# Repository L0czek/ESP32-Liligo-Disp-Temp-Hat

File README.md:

# ESP32 LilyGO Display + Temperature Hat

A KiCad 10 hat for the **LilyGO T-Relay-8** (ESP32, 8 relays). It adds 8 thermocouple
inputs, heater current measurement, a 1-Wire port and a connector for a front panel
(1.3" SH1106 OLED with rotary encoder and buttons).

- Base board: [LilyGO T-Relay-8](https://www.amazon.pl/dp/B0B6TY79WN) —
  [vendor repo](https://github.com/Xinyuan-LilyGO/LilyGo-T-Relay) (schematic, DXF outline, pinmap)
- Front panel: [1.3" SH1106 OLED with encoder and buttons](https://allegro.pl/oferta/wyswietlacz-oled-1-3-sh1106-bialy-z-enkoderem-przyciskami-panel-sterowania-18116662587)
- Load: 24 V heaters switched by the T-Relay relays, about 18.75 A in total: several heaters, each under 10 A, one per relay

> **Branches.** `master` is the current board: routed, 0 unconnected, no DRC errors on copper.
> `hand-routed` is the first hand routing exactly as drawn. `scripted-routing` is an earlier,
> fully scripted board with a different layout. Both are kept for reference only.

## Blocks

| Block | Parts | Notes |
|---|---|---|
| Thermocouple front end | J2–J9, D1–D4, R14–R29, U1, U3 (TMUX1108), U2 (MAX31856) | Each terminal has an ESD clamp and 100 Ω in series (see "Thermocouple input protection"). U1 muxes the `+` legs, U3 the `−` legs, into one MAX31856 over SPI. Input filter: R1 100 Ω, R2 300 Ω, C1 100 nF differential, C2/C3 10 nF to GND. |
| I/O expander | U4 (PCF8574A), U5 (74LVC1G04), JP1–JP3 | Mux address and enable, MAX31856 status, two panel buttons. |
| Front panel | J10 (1x9 socket) | I²C display, encoder, buttons. The panel plugs in on a right-angle header and lies flat past the hat's lower edge. |
| Heater current | J11, R6 (shunt), U6 (INA226) | High-side shunt in the +24 V feed, read over I²C. See "Heater current sensing". |
| 1-Wire | J12 (JST PH 3-pin), R12, U7, U8 | External DS18B20 probes on J12, plus two on-board DS18B20Z (U7, U8) for cold-junction sensing. Recommended; the board works without them, less accurately. |
| Supply | L1, C10–C14 | `VCC` = 3V3 from the T-Relay; `VAA` = analog rail for U2, filtered by ferrite bead L1. |

## J1: connection to the T-Relay-8

J1 is a 2x11 socket soldered on the **bottom** of the hat, facing down onto the T-Relay's pin
header P5. Its footprint is on the back side of the board, so the board file shows what is
really built: pads, silkscreen, courtyard and 3D model are all on the bottom.

**J1's pin numbers are the same as LilyGO's P5 pin numbers.** J1 pin n mates with P5 pin n.
Checked against the official T-Relay-8 schematic (`Schematic/T_Relay8_ESP32.pdf`, header P5),
the vendor pinmap image and the silkscreen labels in the vendor DXF; all three agree. The
schematic and the pinmap were downloaded and compared again on 2026-11-12. This is a check
against documents only: no real T-Relay was at hand to put a meter on. On the
board, pad 2 (3V3) is at (121.54, 95.89) and pad 1 (GND) at (121.54, 93.35), which is the
right-hand end of the header seen from above with the relays on the left.

(Before 2026-11-12 the footprint sat on the front layer with the two rows numbered the other
way round, pin 1 = 3V3. That was electrically the same but drew the socket on the wrong side.)

### How the hat sits on the T-Relay-8

From the vendor DXF and STEP model (T-Relay board is 85 × 170 mm). With J1 mated, a point on
the hat at (x, y) is above the T-Relay point (x − 41.54, y − 19.99) mm, measured from the
T-Relay's top-left corner with the relays on the left.

- **The hat's top and right edges are flush with the T-Relay's.** The outline is 46.0 × 99.7 mm
  (it was 48.3 mm wide; 2.3 mm were cut off on the right). It covers the T-Relay from
  x = 39.0 mm to the right edge and from the top edge down to y = 99.7 mm.
  - Relative to the original design, everything except J1 sits 3.3 mm further left and
    3.5 mm further down on the sheet; J1 and `REF1` did not move.
  - The T-Relay's top edge is at hat y = 19.99 and its right edge at hat x = 126.54.
- **Relays** are 15.7 mm tall and end at x = 37.7 mm, 1.3 mm from the hat's left edge.
- **The ESP32 antenna is not under the hat.** The module sits at T-Relay x = 59–77.5 mm,
  y = −6.4 to 25.6 mm; its antenna end sticks out past the T-Relay's top edge, where the hat
  stops.
- **Mounting holes** are M3 with a 6.4 mm pad, as in the original. H1 is at (122.7, 23.8) and
  H3 at (122.9, 104.1): both had to move in from the cut edge, and H3 also up, because the
  corner beside J10 is too narrow for it. H2 and H4 are at their original places.
  - H2 is above the T-Relay's reset button (S1), so it cannot take a resting spacer. Known
    and accepted: H2 stays where it is, without a spacer. The button is covered by the hat;
    the T-U2T programmer resets the ESP32 through the USB-C connector instead.
  - The other three, the terminal pins, the J11 pins and the parts on the back were checked
    on 2026-11-12 against the vendor STEP model, DXF and top-view photo
    (`image/T-Relay8.jpg`): all clear at an 11 mm gap, and down to about 6 mm. Under H3, H4,
    the J11 pins and the J10 pins the photo shows bare board. No real board was at hand.
  - **H1 is tight:** its pad edge is 0.4 mm from the ESP32 module in the model, and in the
    photo the spacer reaches the module's edge pads to within the 1 mm accuracy of the
    overlay. A nylon spacer there is harmless; a metal one is not.
  - Two of the T-Relay's own 4 mm mounting holes are under the hat, at (91.57, 37.57) and
    (89.64, 93.44): screw the T-Relay down before plugging the hat on.
  - Plain 4 mm holes (the T-Relay's size) were tried and do not help: the stock footprint's
    keep-out is 8.5 mm across, more than the M3 pad, and H4 would not fit between J9 and J10.
  - **Use nylon spacers.** The spacers only rest on the T-Relay's surface and the hole pads
    are GND, so a metal spacer could wear through the solder mask onto a track.
- **J12 sits above the ESP32 module's top end**, so the 1-Wire cable leaves across the antenna.
  This was looked at and accepted; moving J12 to the top-left corner was tried and rejected.

| J1 = P5 pin | ESP32 | Signal | Notes |
|---|---|---|---|
| 1, 3 | GND | GND | |
| 2, 4 | 3V3 | VCC | |
| 5 | IO14 | TC_SCK | LilyGO names this net `GPIO14/CLK` |
| 6 | IO2 | TC_MISO | Boot strap. LilyGO: `GPIO2/MISO` |
| 7 | IO15 | TC_MOSI | Boot strap. LilyGO: `GPIO15/MOSI` |
| 8 | IO4 | TC_CS | Pulled up by R13 (4.7 kΩ) so the MAX31856 stays deselected, and off IO2, during boot |
| 9 | IO35 | ENCODER_B | Input-only |
| 10–14 | NC | — | Not connected on the T-Relay |
| 15 | IO39 | JOYSTICK_PUSH | Input-only. See note below. |
| 16 | IO36 | free | Input-only, ADC1. See note below. |
| 17 | IO34 | ENCODER_A | Input-only |
| 18 | GND | GND | |
| 19 | IO26 | EXPANDER_INT | Pulled up by R3 |
| 20 | IO27 | I2C_SDA | |
| 21 | IO22 | ONEWIRE | The only free bidirectional pin; 1-Wire needs one |
| 22 | IO23 | I2C_SCL | |

- IO34, IO35, IO36 and IO39 are input-only and have no internal pull-ups or pull-downs.
  The front panel provides 10 kΩ pull-ups for the encoder and push button.
- IO36 and IO39 can see very short spurious low pulses when the ESP32's ADC is used or Wi-Fi
  runs with modem sleep (documented by Espressif). Do not use an edge interrupt on
  JOYSTICK_PUSH without debouncing; polling or a debounce of a millisecond or more is enough.
  This is why the push button, not an encoder phase or the expander interrupt, sits on IO39.
- On the T-Relay-8 none of the header GPIOs connect to anything else on the board.
  Relays use IO21, IO19, IO18, IO5, IO12, IO13, IO32, IO33; IO25 is the red LED.

## Heater current sensing

```
PSU+ → J11.1 (24V_IN) → R6 → J11.2 (24V_OUT) → relay COMs → heater → PSU−
```

- The hat sits in the positive feed. No heater current flows in the hat's GND.
- **PSU− must be connected to the T-Relay's GND.** The hat has no terminal for PSU−, so the
  INA226 measures the 24 V rail against the T-Relay's ground. Powering the T-Relay from the
  same 24 V supply does this automatically. With the T-Relay on USB or on a separate isolated
  supply while the heater supply is live, the INA226 inputs float outside their −0.3 to 36 V
  range: readings are meaningless and the chip can be damaged. The T-Relay accepts 12–24 V DC,
  and the plan is to run it from the heater supply, but that is not confirmed: treat this
  as an installation rule.
- J11 is a Phoenix MKDS5/2-6.35 screw terminal block (fixed, not pluggable).
- R6 is a 1 mΩ 4-terminal (Kelvin) shunt, Vishay WSK2512 footprint. Pads 1/4 carry the current,
  pads 2/3 go only to the INA226 inputs. At 18.75 A: 18.75 mV, 0.35 W.
- U6 is an INA226AIDGS at I²C address `0x40` (A0 = A1 = GND), powered from `VCC`, decoupled by C14.
  `Vbus` is on `24V_OUT`, so firmware can also read the supply voltage after the shunt.
  The `Alert` pin is not connected: firmware polls over I²C, and the relays are driven by the
  ESP32 anyway, so a hardware alert would not switch anything off faster.
- R7/R8 (10 Ω) and C15 (100 nF) filter the sense inputs (TI's recommended input filter, corner
  about 80 kHz). They keep relay switching spikes and RF out of the converter and limit current
  into the inputs during transients. 10 Ω is TI's upper limit; the gain error it adds is negligible.
- The review asked for 2 mΩ / 3 W. 1 mΩ was chosen to keep the dissipation low (0.35 W);
  resolution is still about 2.5 mA per LSB.
- Two parts fit (see "BOM"): the true four-terminal Vishay WSK2512 from Mouser, which the
  footprint was drawn for, or an ordinary two-terminal 1 mΩ strip resistor from TME, which
  works on the same pads with a gain error of a few percent.

The board controls several heaters independently, one per relay, each under 10 A; 18.75 A
(450 W at 24 V) is their **sum** (confirmed by the user, 2026-11-12). `24V_OUT` feeds the COM
terminals of all heater relays, and J11 and R6 carry the total.

- The relays are HRS4H-S-DC5V, rated 10 A at 24 V DC per contact (vendor datasheet
  `docs/HRS4-DC5V.pdf`). A single 18.75 A heater on one relay would not be acceptable.
- The INA226 measures the total only. Firmware can get a single heater's current from the
  step in the reading when that relay switches.

## Thermocouple input protection

**Use insulated (ungrounded-junction) thermocouple probes only.** The protection below covers
static discharge and switching spikes. It does not cover a thermocouple line held on 24 V:
that would destroy the clamp and probably the multiplexer.

```
terminal J2–J9 ──────┬── 100 Ω ── TCn± ── TMUX1108 ── ... ── MAX31856
                     │
              ESD clamp to GND
```

- The MAX31856 inputs withstand ±45 V, but the TMUX1108 in front of it only allows −0.5 V to
  VDD + 0.5 V on its signal pins and is rated for 2 kV ESD, so the multiplexers are the weak point.
- D1–D4: Nexperia PESD5V0L4UG, four clamps per package, one package per pair of terminals
  (D1: J2/J3, D2: J4/J5, D3: J6/J7, D4: J8/J9). Place each one right at its terminals.
  The schematic symbol is KiCad's generic 4-diode array (`SP0504BAJT`: same pinout, same
  SOT-353 footprint) with the value set to PESD5V0L4UG, because the library's own PESD symbol
  is split into four separate diode units and reads badly.
- R14–R29: 100 Ω in each line, between the clamp and the multiplexer.
- R2 is 300 Ω, not 100 Ω. The bias point is at the multiplexer output, so both added 100 Ω
  resistors of a channel end up in the T+ path (R1 + 2 × 100 Ω). The MAX31856 datasheet
  ("Effect of Series Resistance") says to match the two paths: offset = I_B × ΔR_S + ΔI_B × R_S,
  with I_B up to 65 nA. Unmatched, 200 Ω would add up to 13 µV; matched, about 2 µV (0.05 °C, type K).
- Series resistance per input stays far below 5 kΩ, so the fast open-circuit detection mode
  (`OCFAULT = 01`) still applies.
- Clamp leakage (25 nA per TME's listing, at 5 V; lower at the 0.7 V the lines sit at) flows
  through 100 Ω at most: under 3 µV.

Considered and not used: 2.2 kΩ + BAV199 rail clamps + 100 Ω per line, which would survive a
continuous 24 V on any line. It needs 48 parts, R2 of about 4.75 kΩ, the slower open-circuit
mode, and costs up to about 20 µV (0.5 °C) worst case.

## Cold-junction sensing

A thermocouple reading is the tip temperature minus the temperature of the terminals J2–J9,
so an error in the terminal temperature goes into every reading one for one. The MAX31856
uses its own internal sensor for this, which measures the chip, not the terminals.

U7 and U8 are two DS18B20Z on the `ONEWIRE` bus (shared with J12, pulled up by R12). Firmware
can read them, interpolate along the terminal row and write the result into the MAX31856's
cold-junction register in place of the internal sensor.

- **Fit them (recommended).** U2 is about 28 mm from the terminals, and the terminals sit
  1.3 mm from the relays, which warm up when energised. U2's internal sensor does not see
  that.
- **The board still works without them.** Leave U7, U8, C16 and C17 unfitted and let the
  MAX31856 use its internal sensor; nothing else changes, and 1-Wire on J12 is unaffected.
  They are not flagged DNP in the schematic. What it costs:
  - Every channel reads wrong by the temperature difference between U2 and its terminal,
    one for one. Expect a few °C; this has not been measured.
  - The error is not a fixed offset. It depends on which relays are on and for how long,
    and it differs along the row, so it cannot be calibrated out.
  - Fine for coarse control or for watching trends; not for readings that have to be
    right to a degree.
- **Moving U2 closer was looked at and rejected** (2026-11-12). The only free spot is
  mid-row beside U3, about 12 mm from the terminal pins. It means moving eight parts and
  rerouting about 16 nets, and one sensor still cannot see the gradient along a 94 mm row.
  With U7/U8 fitted, U2's position does not matter.
- Known limit: R6 and J11 dissipate about 0.5 W level with J6/J7, mid-row, where the two
  end sensors cannot see it. Worth one measurement at full heater current on the built board.
- Layout: one sensor at each end of the J2–J9 row, close to the terminals, each with its
  capacitor (C16, C17) next to it. Keep the shunt, J11, L1 and the 24 V copper away from the
  terminals and from U2, and group the terminals close to U2 if possible.

## U4 (PCF8574A) port map

Address `0x38` with JP1–JP3 in their default position (A0–A2 to GND).

| Port | Signal | Direction |
|---|---|---|
| P0–P2 | TC_A0–TC_A2 (mux channel n = `TCn` = terminal J(n+2): J2 is channel 0, J9 is channel 7) | out |
| P3 | mux enable, inverted by U5: P3 low = muxes on. High at power-up, so muxes start disabled. | out |
| P4 | JOYSTICK_CONFIRM | in |
| P5 | JOYSTICK_BACK | in |
| P6 | TC_DRDY | in |
| P7 | TC_FAULT | in |

## Firmware notes

- **After switching the thermocouple channel, wait 1–2 ms before starting a conversion.**
  The original review said about 100 µs. Since then each line got 100 Ω and R2 became 300 Ω,
  so C1 (100 nF) now charges through about 610 Ω plus the probe's own resistance: a time
  constant of about 65 µs. Settling a 20 mV step between two channels to 1 µV takes about
  ten time constants, 0.7 ms.

## J10: front panel

| Pin | Signal | Pin | Signal |
|---|---|---|---|
| 1 | JOYSTICK_CONFIRM | 6 | ENCODER_B |
| 2 | I2C_SDA | 7 | JOYSTICK_BACK |
| 3 | I2C_SCL | 8 | GND |
| 4 | JOYSTICK_PUSH | 9 | VCC |
| 5 | ENCODER_A | | |

### Panel module

Generic "1.3 inch OLED + EC11 encoder" module, 9-pin header, about 65 × 35 mm, four M3 holes.
Details below are read from the seller manual's schematic (a low-resolution image of the
generic module, not measured on our unit):

- Display: SH1106, I²C address 0x3C, 3.3 V supply only (no regulator shown).
- I²C: 10 kΩ pull-ups to 3V3 on SDA and SCL on the module.
- Encoder A/B (TRA/TRB) and push (PSH): each has a 10 kΩ pull-up to 3V3, 100 nF to GND
  and a 100 Ω series resistor. Switches close to GND (active-low).
- CON (KEY1) and BAK (KEY0) buttons: 10 kΩ pull-up, 100 nF to GND, switch to GND.
- Header order is CON, SDA, SCL, PSH, TRA, TRB, BAK, GND, VCC, which matches J10 pin 1–9.
  The module's own schematic numbers the header the other way round (pin 1 = 3V3).

**Pin order checked against the module's silkscreen** in the seller's photos (2026-11-12),
both sides:

- Front, left to right with the header along the top edge: `CON SDA SCL PSH TRA TRB BAK GND
  VCC`. The square pad is the VCC end.
- Back, same pads: `CONFIRM OLED_SDA OLED_SCL ENCODER_PUSH ENCODER_A ENCODER_B BACK GND 3V3`.
- J10 pins 1–9 carry exactly these signals in this order.
- A straight header comes loose with the module. It is not used: see below.

Consequences: the hat's pull-ups for the encoder and push button (R9–R11, 10 kΩ) are
back-ups, marked do-not-populate. Fit them only if a panel without pull-ups is used. With the panel connected, the I²C bus already has the
panel's 10 kΩ in parallel with R4/R5.

### How the panel connects

**The panel gets a right-angle 1 × 9 pin header and plugs straight into J10. It lies flat,
as an extension of the hat past its lower edge, screen up.** Nothing changes on the hat.

- **Pin order is right.** Seen from above, the panel lies the same way round as in a front
  photo (header along the top edge, CON on the left), and J10 has pin 1 on the left: CON
  lands on pin 1, VCC on pin 9. This matches the `CON` and `VCC` labels on the hat.
- **Solder the header on the panel's back**, pins pointing out past the header edge. The
  panel then sits about 3 mm above the hat's surface, about 15 mm above the T-Relay.
- **Position** (sheet coordinates): about x = 87.6–154.1, y = 121.4–156.8.
  - 8 mm clear of the relays on the left.
  - Only low parts of the T-Relay are under it (the tallest are 3.8 mm).
  - It ends before the T-Relay's USB-C connector and power terminal.
  - **It sticks out about 28 mm past the right edge of both boards**, because the panel is
    66 mm wide and its header is near its left end.
- **It needs support.** On its own it hangs on the nine pins, and pressing the encoder or
  the buttons levers on them from up to about 45 mm away. The panel's two left mounting
  holes are above the T-Relay and can take spacers of about 15 mm; the two right ones are
  beyond the boards' edge.
- The display reads the right way up for someone standing at the T-Relay's power-input end.
- It covers the lower part of the T-Relay (optocouplers, relay indicator LEDs).

The heights and the stand-off from the hat's edge assume a typical 2.54 mm right-angle
header and were not measured; the mounting-hole positions were read off the photo.

Other ways of connecting it, and why not:

- **A straight header, panel standing up at the hat's edge and facing outwards:** pin order
  reversed, VCC on J10 pin 1, and the panel's corner hits a relay. This is the trap: it is
  what a straight header naturally gives.
- **A straight header, panel hanging down and facing outwards:** right pin order, but it
  needs about 32 mm below J10 and the T-Relay is 12.6 mm below.
- **A 1:1 cable:** also correct electrically (J10 pin 1 to CON … pin 9 to VCC), if the
  panel should go somewhere else, for example on an enclosure's front. A plain pin strip
  is not keyed, so watch which end is pin 1.

## BOM

TME prices are gross PLN at the quantity needed, checked 2026-11-12. Rules used: common
resistor and capacitor values and plain pin headers/sockets are assumed to be on hand and
are only listed, not priced; everything else is the cheapest part that is in stock and sold
in prototype quantities.

The parts are split over two orders, TME and Mouser, because the MAX31856 is only at Mouser.

- TME prices are live from TME's API, gross.
- Mouser prices and stock were read from mouser.pl on 2026-11-12, as displayed there. The
  pages did not say whether VAT is included; Mouser normally shows net prices.
- **→ M** in the TME table marks a part that TME has but that is better bought from Mouser,
  since a Mouser order is needed anyway. The reason is in the notes.

### Order 1: TME

| Ref | Qty | Part | TME | Price | → M | Notes |
|---|---|---|---|---|---|---|
| U1, U3 | 2 | TI TMUX1108PWR, TSSOP-16 | [`TMUX1108PWR`](https://www.tme.eu/pl/details/TMUX1108PWR/) | 2 × 28.29 | **→ M** | TME has only 12 left. Mouser has 5,948 at 19.36 zł. |
| U4 | 1 | TI PCF8574APWR, TSSOP-20 | [`PCF8574APWR`](https://www.tme.eu/pl/details/PCF8574APWR/) | 9.40 | **→ M** | 6.03 zł at Mouser. Stands in for the NXP PCF8574ATS in the schematic, which TME does not list. Pinout checked against TI's datasheet (DGV/PW package, figure 4-3): all 20 pins match the schematic, and the footprint is the same 4.4 mm, 0.65 mm pitch package. |
| U5 | 1 | TI SN74LVC1G04DBVR, SOT-23-5 | [`SN74LVC1G04DBVR`](https://www.tme.eu/pl/details/SN74LVC1G04DBVR/) | 0.64 | | |
| U6 | 1 | TI INA226AIDGSR, VSSOP-10 | [`INA226AIDGSR`](https://www.tme.eu/pl/details/INA226AIDGSR/) | 11.06 | | |
| U7, U8 | 2 | DS18B20Z+, SO-8 | [`DS18B20Z+`](https://www.tme.eu/pl/details/DS18B20Z%2B/) | 2 × 32.94 | | Recommended, not required: see "Cold-junction sensing". C16/C17 go with them. |
| D1–D4 | 4 | Nexperia PESD5V0L4UG, SOT-353 | [`PESD5V0L4UG.115`](https://www.tme.eu/pl/details/PESD5V0L4UG.115/) | 4 × 1.23 | | |
| R6 | 1 | Eaton MSMA2512R0010FEN, 1 mΩ 1 % 2 W metal strip, 2512 | [`MSMA2512R0010FEN`](https://www.tme.eu/pl/details/MSMA2512R0010FEN/) | 2.46 | **→ M** | Works (see "R6 on the four-terminal footprint"), but it is a two-terminal part. Mouser has the part the footprint was drawn for: Vishay WSK25121L000FEA, in the Mouser table. Buy one or the other. |
| L1 | 1 | TDK MPZ2012S601ATD25, 600 Ω at 100 MHz, 2 A, 0805 | [`MPZ2012S601ATD25`](https://www.tme.eu/pl/details/MPZ2012S601ATD25/) | 0.38 | | |
| R2 | 1 | Yageo RC0805FR-07300RL, 300 Ω 1 %, 0805 | [`RC0805FR-07300RL`](https://www.tme.eu/pl/details/RC0805FR-07300RL/) | 0.20 | | Listed because 300 Ω is not an E12 value. |
| J11 | 1 | Phoenix MKDS5/2-6.35, 32 A | [`MKDS5/2-6.35`](https://www.tme.eu/pl/details/MKDS5_2-6.35/) | 8.04 | | Exact fit on the stock `TerminalBlock_MetzConnect_Type701_RT11L02HGLU` footprint (hole size confirmed on the Phoenix drawing by the user). |
| J12 | 1 | JST S3B-PH-SM4-TB | [`S3B-PH-SM4-TB`](https://www.tme.eu/pl/details/S3B-PH-SM4-TB/) | 2.29 | | |
| J12 cable end | 1 + 3 | JST PHR-3 housing and SPH-002T-P0.5L/C crimp contacts | [`PHR-3`](https://www.tme.eu/pl/details/PHR-3/), [`SPH-002T-P0.5L/C`](https://www.tme.eu/pl/details/SPH-002T-P0.5L_C/) | 0.29 + 3 × 0.44 | | Only if the 1-Wire cable is made up by hand. |

Everything in this table: about 163 zł. With the three **→ M** lines moved to Mouser: about 95 zł.

### Order 2: Mouser

| Ref | Qty | Part | Mouser no. | Price | Stock | Notes |
|---|---|---|---|---|---|---|
| U2 | 1 | Analog Devices MAX31856MUD+, TSSOP-14 | `700-MAX31856MUD+` | 53.94 | 4,846 | The reason for this order: TME lists only the MAX31855/MAX31850. |
| J2–J9 | 8 | Phoenix MCV 1,5/2-G-5,08 header (Phoenix no. 1836299) | `651-1836299` | 8 × 3.22 | 1,038 | TME: stock 0. |
| J2–J9 plugs | 8 | Phoenix MC 1,5/2-ST-5,08 BK screw plug, black (Phoenix no. 1981238) | `651-1981238` | 8 × 8.80 | 41 | The usual green one (1836079, `651-1836079`, 9.11) has stock 0 at both TME and Mouser; Mouser expects it on 2026-12-11. The black one is the same plug. |
| R6 | 1 | Vishay WSK25121L000FEA, 1 mΩ 1 % 1 W, four-terminal 2512 | `71-WSK25121L000FEA` | 9.33 | 4,273 | Instead of the TME part: the exact part for the footprint, a true four-terminal shunt. |
| U1, U3 | 2 | TI TMUX1108PWR | `595-TMUX1108PWR` | 2 × 19.36 | 5,948 | Instead of TME, see above. |
| U4 | 1 | TI PCF8574APWR | `595-PCF8574APWR` | 6.03 | 183 | Instead of TME, see above. |

The three lines only Mouser can supply (U2, headers, plugs): about 150 zł. With the three
**→ M** lines as well: about 204 zł.

Every part on the board has a source.

### R6 on the four-terminal footprint

TME sells four-terminal 2512 shunts (Bourns CSS2H/CSI2H-2512K, Vishay WSK2512) only in
reels or lots of 173 and more, so the pick is an ordinary two-terminal strip resistor.

- **It fits and connects correctly.** On the WSK2512 footprint each end has a current pad
  (3.3 × 2.03 mm) and a sense pad (1.4 × 0.76 mm) side by side across the part's width, both
  reaching past the part's end. A 2512 end termination is as wide as the part, so it lands
  on both. The two pads of one end are then joined by the termination itself, which is the
  intended connection.
- **The measurement is still close to four-wire.** The sense track leaves from its own pad
  under the termination, so it does not share the solder joint or the copper that carries
  the 19 A.
- **What is lost:** the sense point is on the termination instead of at the resistive
  element, so the reading includes a little termination resistance. Expect a fixed gain
  error of a few percent and somewhat more drift with temperature than a true
  four-terminal part. Calibrate the gain once in firmware. For monitoring heater current
  this is not a problem.

### Assumed on hand

| Ref | Qty | Value | Footprint |
|---|---|---|---|
| R1, R14–R29 | 17 | 100 Ω | 0805 |
| R3 | 1 | 10 kΩ | 0805 |
| R4, R5, R12, R13 | 4 | 4.7 kΩ | 0805 |
| R7, R8 | 2 | 10 Ω | 0805 |
| C1, C4–C9, C14–C17 | 11 | 100 nF | 0805 |
| C2, C3 | 2 | 10 nF | 0805 |
| C10–C13 | 4 | 22 µF, 10 V or more, X5R/X7R | 1206. If not on hand: [`GRM31CR61E226KE15L`](https://www.tme.eu/pl/details/GRM31CR61E226KE15L/), 25 V X5R, 1.67 at 10 pieces. |
| J1 | 1 | 2 × 11 socket, 2.54 mm, 8.5 mm high, soldered on the **bottom** | |
| P5 on the T-Relay | 1 | 2 × 11 pin header, 2.54 mm | soldered on the T-Relay; with J1 it sets the 11 mm gap |
| J10 | 1 | 1 × 9 socket, 2.54 mm, right-angle | |
| Panel header | 1 | 1 × 9 pin header, 2.54 mm, **right-angle** | soldered on the back of the panel; not the straight header that comes with it |

Not fitted: R9–R11 (10 kΩ, back-up pull-ups, see "Panel module"), JP1–JP3 (solder jumpers).
Mechanical: three M3 nylon spacers, 11 mm, for H1, H3 and H4 (H2 stays empty).
For the panel: two M3 nylon spacers of about 15 mm under its two left mounting holes, length
to be fitted on the real parts.

### Parts considered and dropped

- J11 was first given a generic 9.5 mm footprint with 2 mm holes for the Degson
  `DG638-9.52-02P` (32 A, 4.49 zł). It took 21.6 × 18.9 mm of board and was the main reason
  the layout was tight, so it was replaced by the smaller Phoenix part. Phoenix
  `MKDS3/2-5.08` (24 A) was rejected as too small for a continuous 19 A load.
- R6: the review asked for 2 mΩ. 1 mΩ keeps the dissipation at 0.35 W at 18.75 A.
- J2–J9: the Phoenix headers and plugs cost about 12 zł per channel. The common 5.08 mm
  pluggable blocks (2EDG / MSTB style) cost under 2 zł per channel at TME, but have 1.0 mm
  square pins that do not go into the footprint's 1.2 mm holes, so using them would mean a
  footprint change. Not done; the Phoenix parts are available.

## PCB layout

State: **0 unconnected, no DRC errors on copper** (clearance, shorts, holes, edge, dangling
ends all 0), schematic parity 0, ERC 0. What DRC still lists is 34 silkscreen warnings, all of one kind: the outlines of J9 and J10
cross the board edge by a few hundredths of a millimetre, because both parts sit flush with
it. The fab clips them; nothing is lost.

Placement:

- **The original parts keep their arrangement**: multiplexers U1/U3 beside the converter U2,
  with their decoupling, as in the original design. Everything except J1 sits 3.3 mm further
  left and 3.5 mm further down on the sheet than originally; J1 did not move.
- **The protection column is at x = 91.1–92.7**, 4.7 mm from the terminal pins, in four
  groups (one clamp and four series resistors per pair of terminals). Group 4 (J8/J9) is the
  mirror image of group 1 (J2/J3).
  - The series resistors are level with their terminal pins, except R19 and R24, which sit
    0.57 mm off the pin axis: with R24 level, TC6− and TC7− only fit with 0.2 mm gaps.
- **Cold-junction sensors U7 and U8 are on the back** under the column, at (91.75, 32.06) and
  (91.75, 108.30): mirror images about the middle of the terminal row (y = 70.18). C16 and C17
  sit 4.8 mm above their sensor, at x = 90.54.
- **Heater sensing:** J11 at (117.55, 82.9) with the wire entry facing right, R6 directly
  left of it, then R7, R8, C15, U6 and C14.
- **Pull-ups:** R3–R5 with C8 at the right edge beside U4; R9–R11 above their J10 pins; R12
  at J12; R13 just above J1, on the chip-select track.
- **Mounting holes** H1–H4, see "How the hat sits".

Routing:

- Four layers: front and back for signals, In1 = VCC plane, In2 = GND plane.
  - The planes' own clearance is 0.2 mm, the same as the board's. At 0.3 mm the clearance
    holes of J1's 22 pins merged into one 27 mm slot in both planes; at 0.2 mm about 0.4 mm
    of copper stays between neighbouring pins and both planes are continuous through J1.
- **Every segment is horizontal, vertical or at 45°**, and ends on a pad or via centre.
  Tracks are 0.3 mm; only the Kelvin pair and U6's own short tracks are 0.2 mm.
- **Protection groups** are terminal → series resistor → clamp on the front. The outer line of
  a group runs straight between the pads of the inner resistor to the clamp.
- **Clamp ground vias are outside the clamps**, 1.2–1.5 mm out on the three-pin side, at
  x = 90.94. The group's inner line runs 0.37 mm further left beside the via.
  - At D1 and D4 the via comes out between the pad rows of the sensor on the back; that is
    what fixes the sensors' positions. At U8 the TC7+ track passes between the rows as well.
  - U8's ground pin goes to H4's pad, because the TC7+ track separates it from D4's via.
- **Thermocouple lines to the multiplexers:** the `−` lines run on the front between the
  column and U3; the `+` lines of channels 4–7 run on the back to vias beside U1.
  - Each pair ends on two chips 11 mm apart, so its last stretch is always split. Mean
    distance between the two lines of a pair: channels 0–2 1.0–1.8 mm, channel 3 4.8 mm,
    channels 4–6 3.4–4.2 mm, channel 7 10.6 mm.
  - **TC7+ goes round the outside of the terminal row** (x = 82). Bringing it inside needs
    the lane beside J1's left pins, which `JOYSTICK_CONFIRM` uses on the back, and a
    different order of the three vias beside U1. It was left: the heaters are switched by
    relays on DC, so the loop only sees an occasional switching edge.
- **Heater path:** `24V_IN` and `24V_OUT` zones on both outer layers between J11 and R6 with
  fifteen 0.8 mm stitching vias; Kelvin pair from R6's sense pads to U6.
- **SPI, I²C, 1-Wire and the panel lines go round the heater copper on the right.**
  - On the back, five tracks (SDA, 1-Wire, MOSI, `JOYSTICK_BACK`, MISO) at 0.6 mm pitch, with
    nested corners below the heater copper, then along J1's top row into their pins.
  - On the front, four lanes: CS 123.57, SCK 124.3, `EXPANDER_INT` 125.05, SCL 125.8, at
    least 0.6 mm from the board edge.
- **At J1:**
  - One track per gap between pin columns, centred in the gap (0.27 mm each side), so front
    and back tracks do not lie on top of each other. The exception is the leftmost gap: SDA
    (front) and SCL (back) share it for 1.8 mm, because four signals end on the four
    leftmost pins and there are only two gaps beside them.
  - The strip between the heater copper and J1's top row is 2.5 mm high and carries five
    back-side and three front-side tracks.
  - SCL from U6 changes to the back just above J1; SDA stays on the front.
- **At the pull-ups R3–R5:** `EXPANDER_INT` runs down their left side into R3, and SCL passes
  between R3's pads, because there is no room to go round R3 at the board edge. Their vias
  sit between the pad rows.
- **Tightest spots (0.2–0.25 mm), all fixed by pad geometry:** SDA/SCL at U6's pins (0.5 mm
  pin pitch) and J1's left-hand corner.
- The channel order is the original one (J2 = channel 0 … J9 = channel 7).

Silkscreen, reference designators:

- All 78 are 1.0 mm high, 0.15 mm stroke (the board's minimum text height is 1.0 mm), clear
  of pads, of other parts' bodies, of each other and of via holes.
- **Protection column:** each name directly to the right of its own part, so the names
  follow the stagger of the parts (the user's choice over one aligned column). Where a via
  sits right after the pad the name starts after the via (R16, R18, R21, R22, R28). R19 is
  above its part, R26 is 0.6 mm higher and R24 0.1 mm lower than its part, all because of
  vias; R29 is 0.15 mm higher to leave room for H4's name.
- **J3–J9:** in the gap above each terminal, at x = 84. J2 has no gap above it (board edge),
  so its name stands upright to the right of it.
- **Elsewhere:** horizontal and beside the part, on the side away from its neighbour:
  pairs C12|C10 and C13|C11 outwards, C1–C3 to the right, R3–R5 to the left, JP1–JP3 in a
  row above. Only R6 and R9–R11 are upright, for lack of width.
- **Back:** U7/U8 on the side away from the terminals, C16/C17 above.

Silkscreen, functional labels (board-level text and lines, not part of any footprint, so
"update footprints from library" leaves them alone):

- **Thermocouple channel:** `TC1`…`TC7` beside the terminal's name in the gap above J3–J9;
  `TC0` upright beside J2's name.
- **Thermocouple polarity:** there is no room for a mark at each pin, so there is one
  pictogram, at (97.3–101.9, 97.0–104.6) below J1's left end: a terminal drawn the same way
  round as the real ones, upper pin `-`, lower pin `+`, headed `TC0-7`. Pin 1 (`+`) is the
  lower pin of every terminal.
- **J11:** `OUT COM` above the block (upper terminal, to the relay COMs) and `IN +24V`
  below it (lower terminal, from the supply). J11's own name moved left to make room.
- **J12:** `3V3 GND DQ` below the pads, in pad order. The words are spread wider than the
  2 mm pad pitch, and `3V3` sits left of its pad because of the via below it.
- **J10:** `CON` above pin 1 and `VCC` above pin 9, the two ends of the panel's header.

Other things to know:

- **Footprint `REF1` is the T-Relay-8 reference, as one object.** It holds both the 2D outline
  on `Dwgs.User` (board edge, relays, ESP32 module, header pins, mounting holes, from the vendor
  DXF) and the 3D model (`3d/T-Relay8-ESP32-3D.stp`, LilyGO's own file, unchanged). It has no
  pads, is board-only, is excluded from the BOM and position files, and is locked.
  - Its anchor is the T-Relay's bottom-left corner. If J1 ever moves on the hat, unlock `REF1`
    and move it by the same amount; outline and model move together.
  - The 3D model is drawn 11 mm below the hat's underside. P5 comes unpopulated and is
    soldered by the user, so the gap is set by the parts chosen: a standard 2.54 mm pin
    header (2.5 mm plastic) plus an 8.5 mm socket for J1 gives 11 mm. With other parts,
    change the model's Z offset and the spacer length to match.
- Board coordinates in this README are sheet coordinates in the PCB editor. On 2026-11-12 the
  whole drawing was moved up by 66.04 mm (26 × 2.54) so that the hat and the T-Relay outline
  fit on the A4 sheet; coordinates in commit messages before that are 66.04 mm larger in y.
- When routing, set the track width to "use netclass width". The predefined width list has
  0.2 and 0.4 mm but no 0.3 mm entry.
- Design rules: clearance 0.2 mm, default track 0.3 mm, vias
  0.6/0.3 mm, hole clearance 0.28 mm; net class `Power24V` for the `24V_*` nets. All within
  JLCPCB's standard four-layer limits.
  - One custom rule (`ESP32-Liligo-Disp-Temp-Hat.kicad_dru`): the inner planes keep 0.5 mm
    from the `24V_*` nets, the same as the outer layers, instead of the general 0.2 mm. The
    fifteen stitching vias and both J11 pins pass through the 3V3 and GND planes, and a short
    there would put 24 V on the ESP32's supply. It only changes the plane fill: no part or
    track moved, both planes are still one piece.

## Working on the schematic and board files

- Close the KiCad schematic editor (or use File → Revert afterwards) when the `.kicad_sch`
  file is edited outside KiCad, otherwise a save from KiCad overwrites the change.
- Check each change with:

  ```sh
  kicad-cli sch erc ESP32-Liligo-Disp-Temp-Hat.kicad_sch
  kicad-cli sch export netlist --format orcadpcb2 -o net.txt ESP32-Liligo-Disp-Temp-Hat.kicad_sch
  ```

  and diff the netlist against the one from before the change.
- When the `.kicad_pcb` is edited by script, compare every track's net before and after KiCad
  saves it: KiCad silently re-nets a track that touches copper of another net. Remove old
  tracks before moving the parts they end on.
- ERC is clean (0 violations). VCC, VAA and GND each carry a `PWR_FLAG` because power comes in through J1.

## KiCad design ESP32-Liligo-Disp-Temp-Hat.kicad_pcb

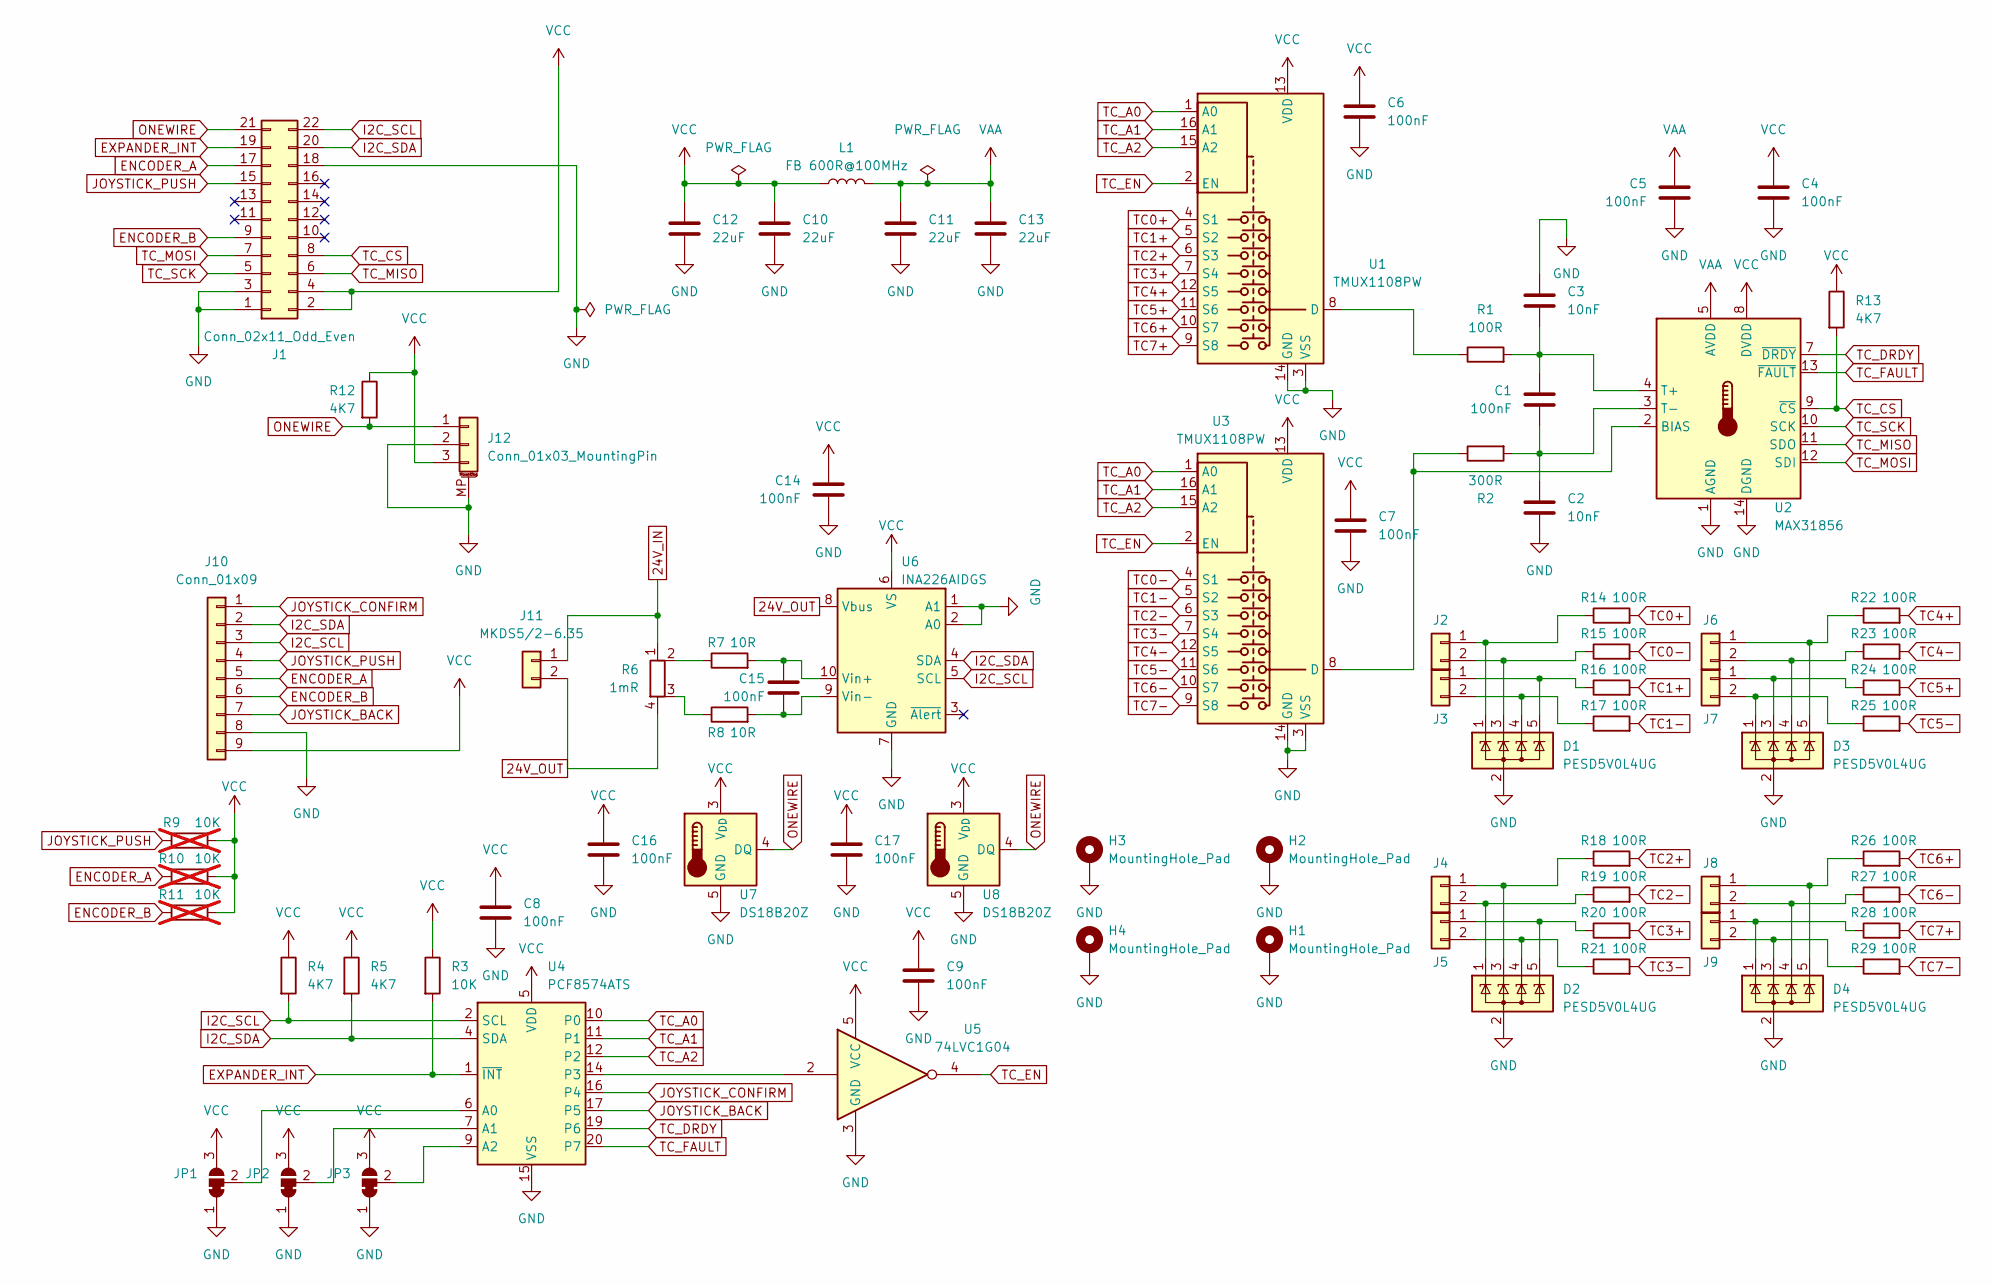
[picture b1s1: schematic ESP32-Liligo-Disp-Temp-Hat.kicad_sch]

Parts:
C1, C4, C5, C6, C7, C8, C9, C14, C15, C16, C17: 100nF; C_0805_2012Metric
C2, C3: 10nF; C_0805_2012Metric
C10, C11, C12, C13: 22uF; C_1206_3216Metric
D1, D2, D3, D4: PESD5V0L4UG; SOT-353_SC-70-5
H1, H2, H3, H4: MountingHole_Pad; MountingHole_3.2mm_M3_Pad_Via
J1: Conn_02x11_Odd_Even; PinSocket_2x11_P2.54mm_Vertical
J2, J3, J4, J5, J6, J7, J8, J9: Conn_01x02; PhoenixContact_MCV_1,5_2-G-5.08_1x02_P5.08mm_Vertical
J10: Conn_01x09; PinSocket_1x09_P2.54mm_Horizontal
J11: MKDS5/2-6.35; TerminalBlock_MetzConnect_Type701_RT11L02HGLU_1x02_P6.35mm_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
J12: Conn_01x03_MountingPin; JST_PH_S3B-PH-SM4-TB_1x03-1MP_P2.00mm_Horizontal
JP1, JP2, JP3: SolderJumper_3_Bridged12; SolderJumper-3_P1.3mm_Bridged12_RoundedPad1.0x1.5mm
L1: FB 600R@100MHz; L_0805_2012Metric
R1, R14, R15, R16, R17, R18, R19, R20, R21, R22, R23, R24, R25, R26, R27, R28, R29: 100R; R_0805_2012Metric
R2: 300R; R_0805_2012Metric
R3: 10K; R_0805_2012Metric
R4, R5, R12, R13: 4K7; R_0805_2012Metric
R6: 1mR; R_Shunt_Vishay_WSK2512_6332Metric_T2.21mm
R7, R8: 10R; R_0805_2012Metric
R9, R10, R11: 10K; R_0805_2012Metric; not fitted
U1, U3: TMUX1108PW; TSSOP-16_4.4x5mm_P0.65mm
U2: MAX31856; TSSOP-14_4.4x5mm_P0.65mm
U4: PCF8574ATS; SSOP-20_4.4x6.5mm_P0.65mm
U5: 74LVC1G04; SOT-23-5
U6: INA226AIDGS; TSSOP-10_3x3mm_P0.5mm
U7, U8: DS18B20Z; SOIC-8_3.9x4.9mm_P1.27mm

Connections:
24V_IN: J11.1, R6.1
24V_OUT: J11.2, R6.4, U6.8 (Vbus)
ENCODER_A: J1.17, J10.5, R10.1
ENCODER_B: J1.9, J10.6, R11.1
EXPANDER_INT: J1.19, R3.2, U4.1 (~INT)
GND: C2.2, C3.1, C4.2, C5.2, C6.2, C7.2, C8.2, C9.2, C10.2, C11.2, C12.2, C13.2, C14.2, C16.2, C17.2, D1.2 (A), D2.2 (A), D3.2 (A), D4.2 (A), H1.1 (1_1), H2.1 (1_1), H3.1 (1_1), H4.1 (1_1), J1.1, J1.3, J1.18, J10.8, J12.2, J12.MP (MountPin), JP1.1 (A), JP2.1 (A), JP3.1 (A), U1.3 (VSS), U1.14 (GND), U2.1 (AGND), U2.14 (DGND), U3.3 (VSS), U3.14 (GND), U4.15 (VSS), U5.3 (GND), U6.1 (A1), U6.2 (A0), U6.7 (GND), U7.5 (GND), U8.5 (GND)
I2C_SCL: J1.22, J10.3, R4.2, U4.2 (SCL), U6.5 (SCL)
I2C_SDA: J1.20, J10.2, R5.2, U4.4 (SDA), U6.4 (SDA)
JOYSTICK_BACK: J10.7, U4.17 (P5)
JOYSTICK_CONFIRM: J10.1, U4.16 (P4)
JOYSTICK_PUSH: J1.15, J10.4, R9.1
unnamed: D1.1 (K), J2.1, R14.1
unnamed: D1.3 (K), J2.2, R15.1
unnamed: D1.5 (K), J3.1, R16.1
unnamed: D1.4 (K), J3.2, R17.1
unnamed: D2.3 (K), J4.1, R18.1
unnamed: D2.1 (K), J4.2, R19.1
unnamed: D2.5 (K), J5.1, R20.1
unnamed: D2.4 (K), J5.2, R21.1
unnamed: D3.5 (K), J6.1, R22.1
unnamed: D3.4 (K), J6.2, R23.1
unnamed: D3.3 (K), J7.1, R24.1
unnamed: D3.1 (K), J7.2, R25.1
unnamed: D4.5 (K), J8.1, R26.1
unnamed: D4.4 (K), J8.2, R27.1
unnamed: D4.1 (K), J9.1, R28.1
unnamed: D4.3 (K), J9.2, R29.1
unnamed: JP1.2 (C), U4.6 (A0)
unnamed: JP2.2 (C), U4.7 (A1)
unnamed: JP3.2 (C), U4.9 (A2)
unnamed: R6.2, R7.1
unnamed: R6.3, R8.1
unnamed: R1.1, U1.8 (D)
unnamed: R2.1, U2.2 (BIAS), U3.8 (D)
unnamed: C1.1, C3.2, R1.2, U2.4 (T+)
unnamed: C1.2, C2.1, R2.2, U2.3 (T-)
unnamed: U4.14 (P3), U5.2
unnamed: C15.1, R7.2, U6.10 (Vin+)
unnamed: C15.2, R8.2, U6.9 (Vin-)
ONEWIRE: J1.21, J12.1, R12.2, U7.4 (DQ), U8.4 (DQ)
TC0+: R14.2, U1.4 (S1)
TC0-: R15.2, U3.4 (S1)
TC1+: R16.2, U1.5 (S2)
TC1-: R17.2, U3.5 (S2)
TC2+: R18.2, U1.6 (S3)
TC2-: R19.2, U3.6 (S3)
TC3+: R20.2, U1.7 (S4)
TC3-: R21.2, U3.7 (S4)
TC4+: R22.2, U1.12 (S5)
TC4-: R23.2, U3.12 (S5)
TC5+: R24.2, U1.11 (S6)
TC5-: R25.2, U3.11 (S6)
TC6+: R26.2, U1.10 (S7)
TC6-: R27.2, U3.10 (S7)
TC7+: R28.2, U1.9 (S8)
TC7-: R29.2, U3.9 (S8)
TC_A0: U1.1 (A0), U3.1 (A0), U4.10 (P0)
TC_A1: U1.16 (A1), U3.16 (A1), U4.11 (P1)
TC_A2: U1.15 (A2), U3.15 (A2), U4.12 (P2)
TC_CS: J1.8, R13.2, U2.9 (~CS)
TC_DRDY: U2.7 (~DRDY), U4.19 (P6)
TC_EN: U1.2 (EN), U3.2 (EN), U5.4
TC_FAULT: U2.13 (~FAULT), U4.20 (P7)
TC_MISO: J1.6, U2.11 (SDO)
TC_MOSI: J1.7, U2.12 (SDI)
TC_SCK: J1.5, U2.10 (SCK)
VAA: C5.1, C11.1, C13.1, L1.2, U2.5 (AVDD)
VCC: C4.1, C6.1, C7.1, C8.1, C9.1, C10.1, C12.1, C14.1, C16.1, C17.1, J1.2, J1.4, J10.9, J12.3, JP1.3 (B), JP2.3 (B), JP3.3 (B), L1.1, R3.1, R4.1, R5.1, R9.2, R10.2, R11.2, R12.1, R13.1, U1.13 (VDD), U2.8 (DVDD), U3.13 (VDD), U4.5 (VDD), U5.5 (VCC), U6.6 (VS), U7.3 (V_{DD}), U8.3 (V_{DD})

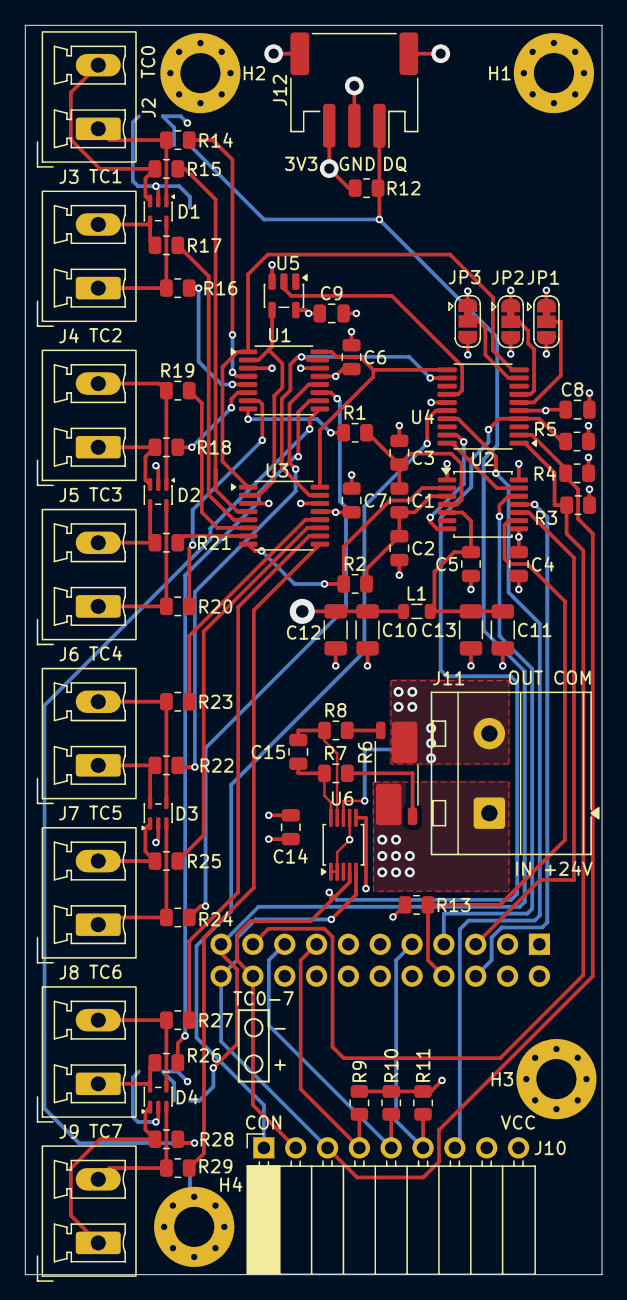
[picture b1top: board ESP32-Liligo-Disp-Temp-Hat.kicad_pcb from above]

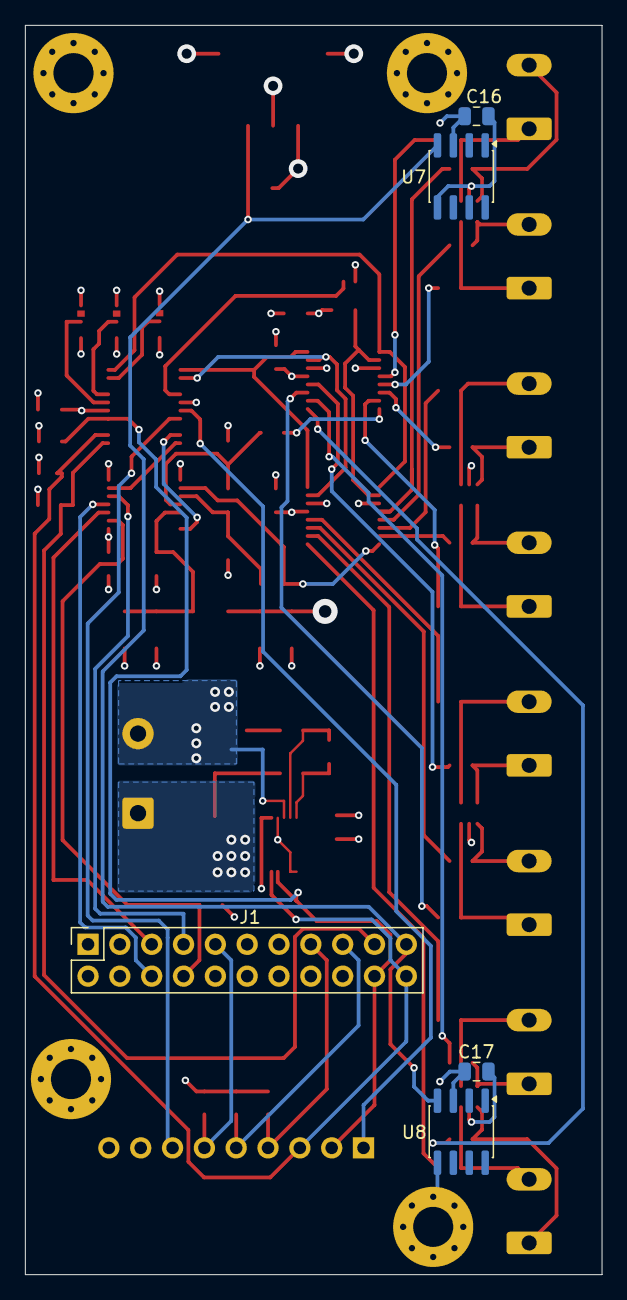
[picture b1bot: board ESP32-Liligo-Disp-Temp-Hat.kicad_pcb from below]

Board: 4 copper layers, 46.0 x 99.7 mm, 79 parts (5 on the bottom side), 68 nets.

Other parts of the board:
REF1: T-Relay-8 reference model
